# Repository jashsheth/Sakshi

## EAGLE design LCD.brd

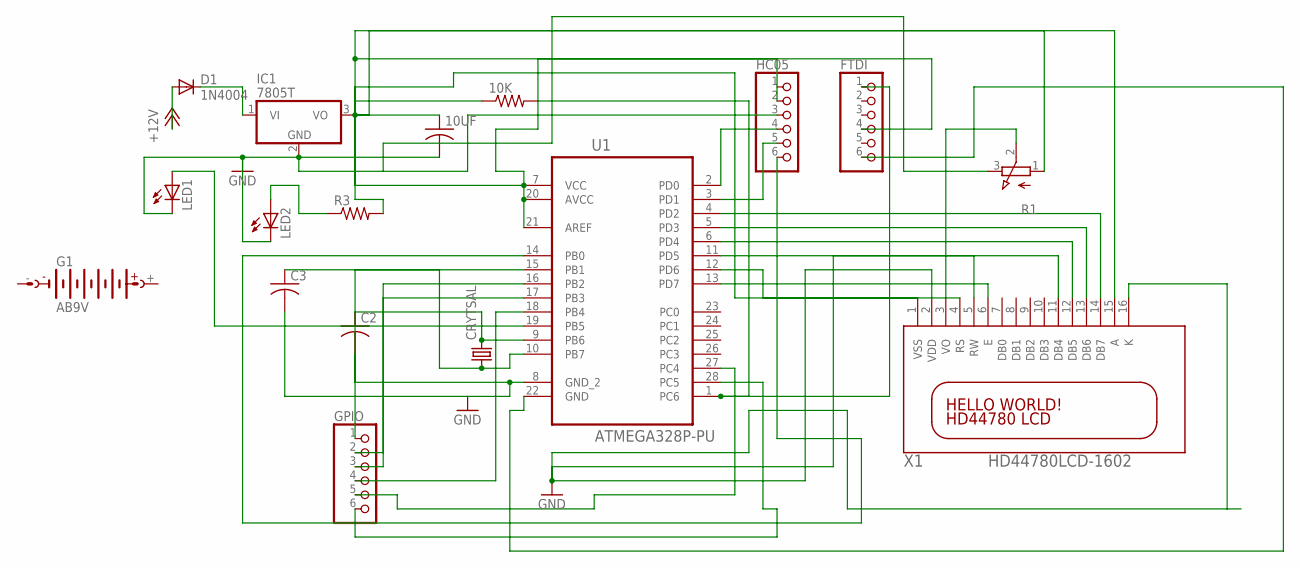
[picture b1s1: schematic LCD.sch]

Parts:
10K: R-US_0204/5; 0204/5
10UF: C-US050-025X075; C050-025X075
C2, C3: C-US025-024X044; C025-024X044
CRYTSAL: CRYSTALHC49U-V; HC49U-V
D1: 1N4004; DO41-10
FTDI: PINHD-1X6-3.5MM; 1X06-3.5MM
G1: AB9V
GPIO: PINHD-1X6-3.5MM; 1X06-3.5MM
HC05: PINHD-1X6-3.5MM; 1X06-3.5MM
IC1: 7805T; TO220H
LED1, LED2: LED5MM
R1: 3RP/1610N
R3: R-US_0204/5; 0204/5
U1: ATMEGA328P-PU; DIP254P762X457-28
X1: HD44780LCD-1602; LCD1602

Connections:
+12V: D1.A
GND: 10UF.2, HC05.3, IC1.2 (GND), LED1.K (C), LED2.K (C), R1.3 (E)
unnamed: R1.2 (S), X1.3 (VO)
unnamed: 10K.1, 10UF.1, FTDI.4, HC05.2, IC1.3 (VO), R1.1 (A), R3.2, U1.7 (VCC), U1.20 (AVCC), U1.21 (AREF), X1.15 (A)
unnamed: GPIO.1, U1.15 (PB1)
unnamed: 10K.2, FTDI.1, U1.1 (PC6)
unnamed: C2.1, CRYTSAL.2, U1.9 (PB6)
unnamed: C3.1, CRYTSAL.1, U1.10 (PB7)
unnamed: C2.2, C3.2, U1.8 (GND_2)
unnamed: U1.4 (PD2), X1.14 (DB7)
unnamed: U1.5 (PD3), X1.13 (DB6)
unnamed: U1.6 (PD4), X1.12 (DB5)
unnamed: U1.12 (PD6), X1.4 (RS)
unnamed: U1.13 (PD7), X1.6 (E)
unnamed: U1.11 (PD5), X1.11 (DB4)
unnamed: GPIO.2, U1.16 (PB2)
unnamed: FTDI.6, U1.22 (GND)
unnamed: D1.C, IC1.1 (VI)
unnamed: HC05.4, U1.2 (PD0)
unnamed: HC05.5, U1.3 (PD1)
unnamed: HC05.6, U1.14 (PB0)
unnamed: LED2.A, R3.1
unnamed: LED1.A, U1.19 (PB5)
unnamed: GPIO.3, U1.17 (PB3)
unnamed: GPIO.4, U1.18 (PB4)
unnamed: GPIO.5, U1.27 (PC4)
unnamed: GPIO.6, U1.28 (PC5)
VDD: X1.2 (VDD), X1.5 (RW), X1.16 (K)
VSS: X1.1 (VSS)

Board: 2 copper layers, 17 parts (0 on the bottom side), 27 nets, no tracks yet.

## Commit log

2019-01-12 Sakshi
2020-09-11 UV rep
